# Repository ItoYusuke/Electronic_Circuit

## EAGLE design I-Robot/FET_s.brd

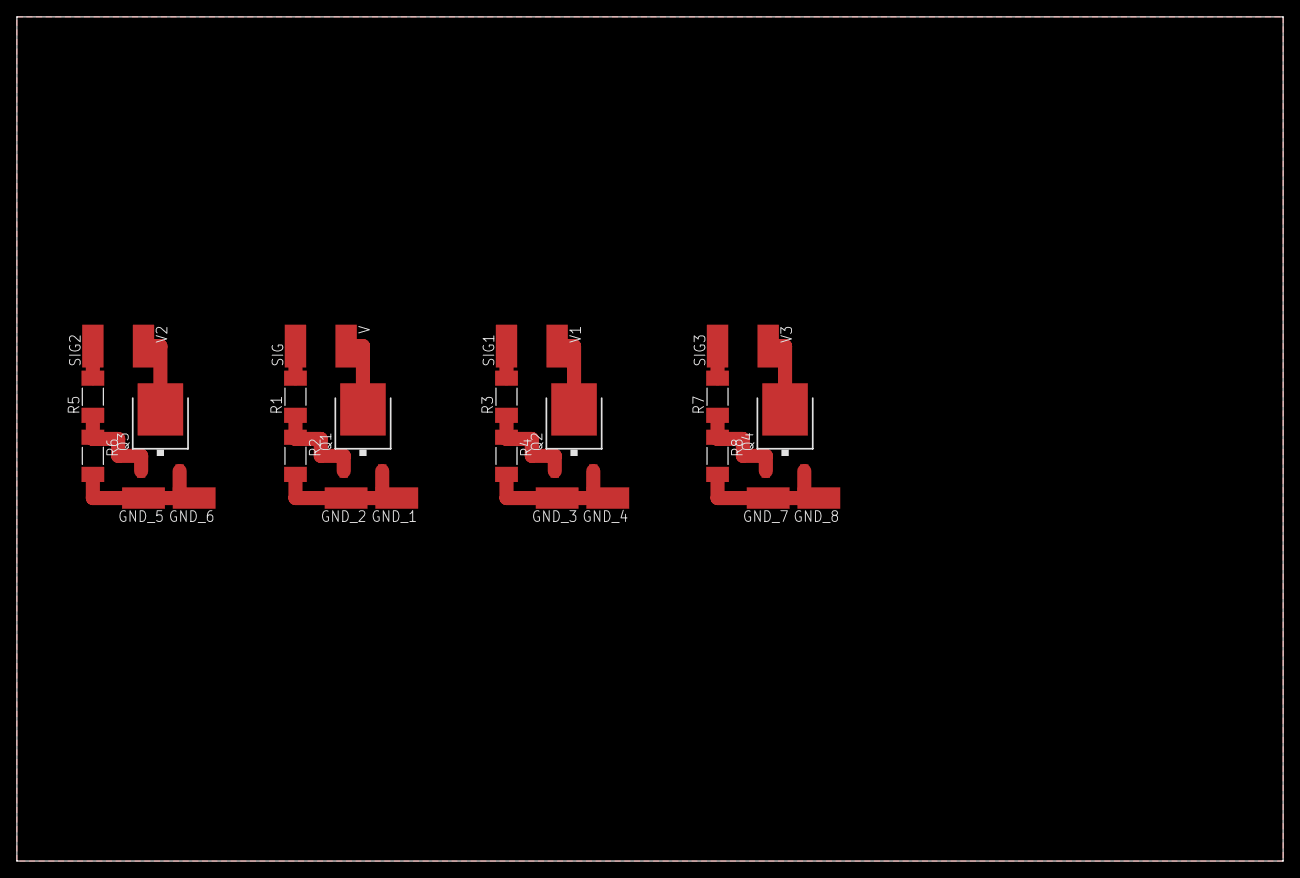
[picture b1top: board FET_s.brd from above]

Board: 2 copper layers, 150.0 x 100.0 mm, 28 parts (0 on the bottom side), 16 nets.

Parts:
GND_1, GND_2, GND_3, GND_4, GND_5, GND_6, GND_7, GND_8: SMD2,54-5,08
Q1, Q2, Q3, Q4: FDD4141TO252; TO252
R1, R2, R3, R4, R5, R6, R7, R8: 1k; R2010
SIG, SIG1, SIG2, SIG3: SMD2,54-5,08
V, V1, V2, V3: SMD2,54-5,08

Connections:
+5V: Q1.3, V.1
+5V1: Q2.3, V1.1
+5V2: Q3.3, V2.1
+5V3: Q4.3, V3.1
unnamed: Q1.1, R1.1, R2.1
unnamed: R1.2, SIG.1
unnamed: Q2.1, R3.1, R4.1
unnamed: R3.2, SIG1.1
unnamed: Q3.1, R5.1, R6.1
unnamed: R5.2, SIG2.1
unnamed: Q4.1, R7.1, R8.1
unnamed: R7.2, SIG3.1
S$1: GND_1.1, GND_2.1, Q1.2, R2.2
S$2: GND_3.1, GND_4.1, Q2.2, R4.2
S$3: GND_5.1, GND_6.1, Q3.2, R6.2
S$4: GND_7.1, GND_8.1, Q4.2, R8.2
